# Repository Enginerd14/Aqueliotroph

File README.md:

# Aqueliotroph
Automated plant watering and sun tracking system to optimise conditions for growth

I made this project becuase I always forget to water my plants and they never get enough sunlight. As a result they never survive :(. The Aqueliotroph system directly combats this by moving the plant to optimise light and watering the plant when soil mositure is low. 

Inspiration behind the Name: 

## 3D model

## Schematic

## PCB

# Parts List

> **Note:** Only the PCB needs to be purchased. I already have all other parts available, so the cost should only be around **£5 / $7**.

| Item | Qty | Need to Buy | Price (£) | Link | Total (£) | Total ($) |
|---|---:|:---:|---:|---:|---:|---
| 600mm Aluminium extrusion | 1 | No | £7.00 | [Al extrusion 600mm](https://www.ebay.co.uk/itm/305167092557?var=604105049024) |52.67 |71.84
| Belt Pulley | 1 | No | £4.99 | [Belt Pulley](https://www.aliexpress.com/item/1005010636842055.html) |
| Belt idler | 1 | No | £3.85 | [Idler Pulley](https://www.aliexpress.com/item/1005008093251681.html) |
| V Wheels | 4 | No | £2.44 | [V Wheels](https://www.aliexpress.com/item/1005004275676552.html) |
| Flexible plastic tube | 1 | No | £1.47 | [PVC tube](https://www.aliexpress.com/item/1005009698880250.html) |
| DC motor | 1 | No | £2.12 | [DC pump 12V 60RPM](https://www.ebay.co.uk/itm/226921983677?var=526075182200) |
| DC Water Pump | 1 | No | £2.48 | [DC water pump](https://www.aliexpress.com/item/1005007587818206.html) |
| Limit Switches | 2 | No | £1.23 | [Limit switches](https://www.aliexpress.com/item/1005005924250789.html) |
| Moisture sensor | 1 | No | £2.59 | [Soil moisture sensor](https://www.ebay.co.uk/itm/235973021747?var=536444158439) |
| Wire | 1m | No | £0.80 | [Wire](https://www.aliexpress.com/item/1005007251965003.html) |
| 470µF and 0.1µF Capacitor | 3 | No | £3.99 | [Capacitors](https://www.ebay.co.uk/itm/227351789982?var=526553493681) |
| LCD Display | 1 | No | £2.21 | [LCD](https://www.aliexpress.com/item/1005005095893869.html) |
| 12V 3A power supply | 1 | No | £4.06 | [Power supply 12V 3A](https://www.aliexpress.com/item/4000494270389.html) |
| L293D | 1 | No | £1.36 | [L293D](https://www.aliexpress.com/item/1005010400118009.html) |
| Arduino Uno | 1 | No | £3.22 | [Arduino Uno R3](https://www.aliexpress.com/item/32768431306.html) |
| LDR | 1 | No | £0.84 | [LDR](https://www.aliexpress.com/item/1005008904534544.html) |
| 10K, 220Ω Resistor | 2 | No | £1.75 | [Resistors](https://www.aliexpress.com/item/32698175464.html) |
| 250K Potentiometer | 1 | No | £1.27 | [Potentiometer](https://www.aliexpress.com/item/1005009882075493.html) |
| **PCB** | **1** | **Yes** | **£5.00** | N/A |

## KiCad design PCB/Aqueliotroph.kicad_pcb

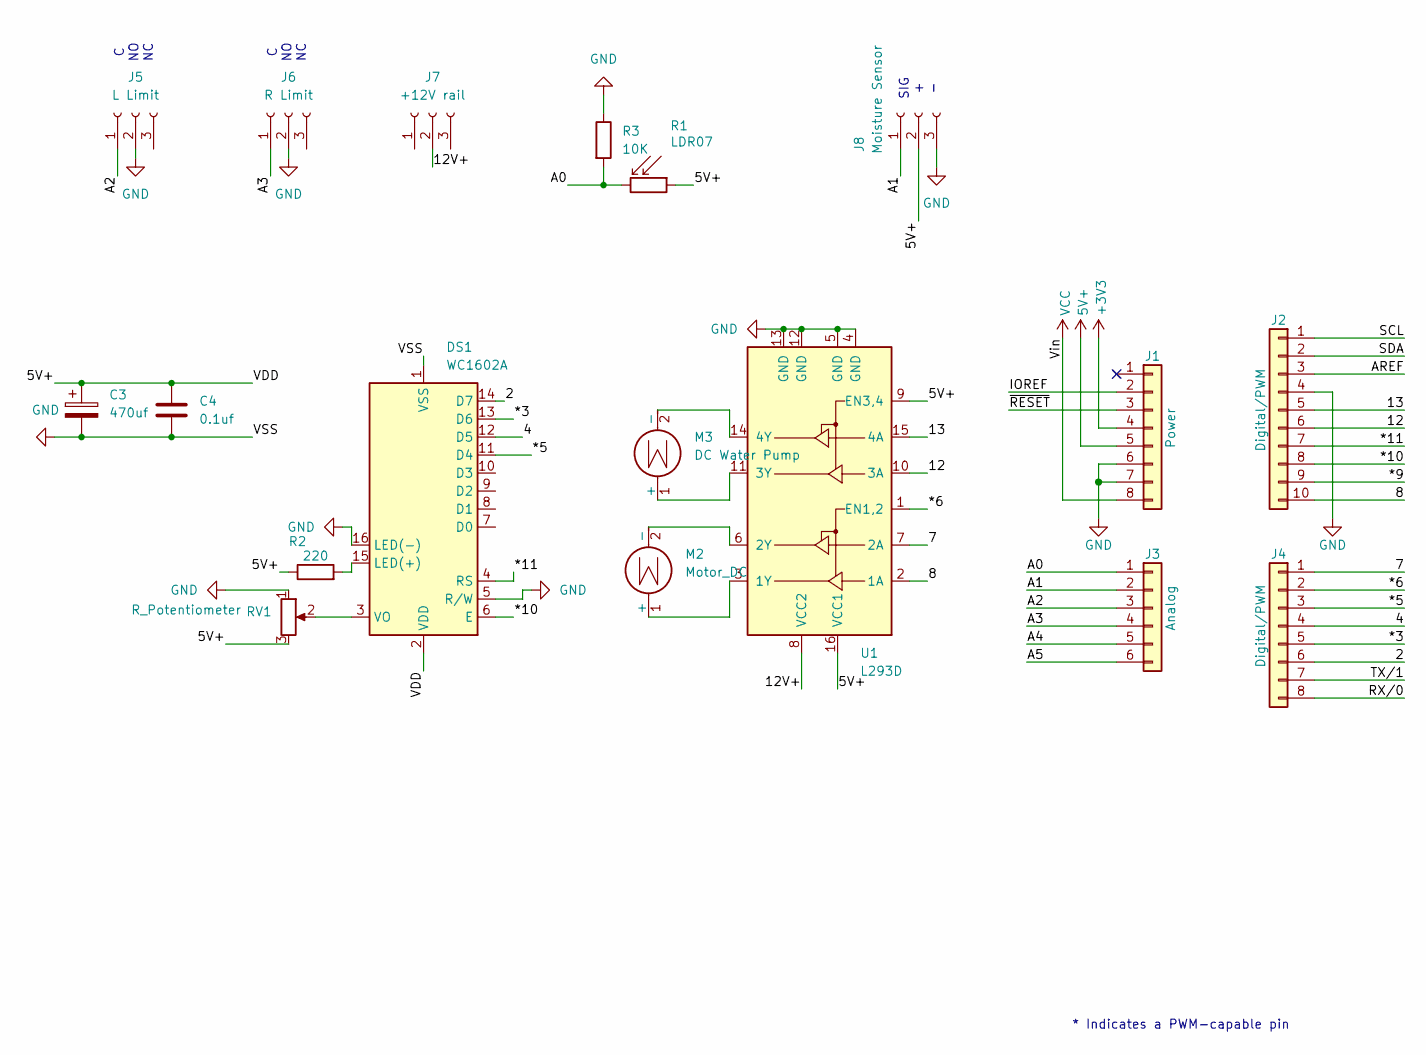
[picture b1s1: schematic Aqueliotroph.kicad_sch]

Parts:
C3: 470uf; C_Radial_D10.0mm_H12.5mm_P5.00mm
C4: 0.1uf; C_Disc_D3.8mm_W2.6mm_P2.50mm
DS1: WC1602A; PinSocket_1x16_P2.54mm_Vertical
J1: Power; PinSocket_1x08_P2.54mm_Vertical
J2: Digital/PWM; PinSocket_1x10_P2.54mm_Vertical
J3: Analog; PinSocket_1x06_P2.54mm_Vertical
J4: Digital/PWM; PinSocket_1x08_P2.54mm_Vertical
J5: L Limit; PinSocket_1x03_P2.54mm_Vertical
J6: R Limit; PinSocket_1x03_P2.54mm_Vertical
J7: +12V rail; PinHeader_1x03_P2.54mm_Vertical
J8: Moisture Sensor; PinSocket_1x03_P2.54mm_Vertical
M2: Motor_DC; PinSocket_1x02_P2.54mm_Vertical
M3: DC Water Pump; PinSocket_1x02_P2.54mm_Vertical
R1: LDR07; PinSocket_1x02_P2.54mm_Vertical
R2: 220; R_Axial_DIN0204_L3.6mm_D1.6mm_P5.08mm_Horizontal
R3: 10K; R_Axial_DIN0204_L3.6mm_D1.6mm_P5.08mm_Horizontal
RV1: R_Potentiometer; Potentiometer_Piher_PT-10-V10_Vertical
U1: L293D; DIP-16_W7.62mm

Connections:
5V+: C3.1, C4.1, DS1.2 (VDD), J1.5, J8.2, R1.1, R2.1, RV1.3, U1.9 (EN3,4), U1.16 (VCC1)
+3V3: J1.4
/2: DS1.14 (D7), J4.6
/4: DS1.12 (D5), J4.4
/7: J4.1, U1.7 (2A)
/8: J2.10, U1.2 (1A)
/12: J2.6, U1.10 (3A)
/12V+: J7.2, U1.8 (VCC2)
/13: J2.5, U1.15 (4A)
/*3: DS1.13 (D6), J4.5
/*5: DS1.11 (D4), J4.3
/*6: J4.2, U1.1 (EN1,2)
/*9: J2.9
/*10: DS1.6 (E), J2.8
/*11: DS1.4 (RS), J2.7
/A0: J3.1, R1.2, R3.2
/A1: J3.2, J8.1
/A2: J3.3, J5.1
/A3: J3.4, J6.1
/A4: J3.5
/A5: J3.6
/AREF: J2.3
/IOREF: J1.2
/RX/0: J4.8
/SCL: J2.1
/SDA: J2.2
/TX/1: J4.7
/~RESET: J1.3
GND: C3.2, C4.2, DS1.1 (VSS), DS1.5 (R/W), DS1.16 (LED(-)), J1.6, J1.7, J2.4, J5.2, J6.2, J8.3, R3.1, RV1.1, U1.4 (GND), U1.5 (GND), U1.12 (GND), U1.13 (GND)
unnamed: DS1.15 (LED(+)), R2.2
unnamed: DS1.3 (VO), RV1.2
unnamed: M2.1 (+), U1.3 (1Y)
unnamed: M2.2 (-), U1.6 (2Y)
unnamed: M3.1 (+), U1.11 (3Y)
unnamed: M3.2 (-), U1.14 (4Y)
VCC: J1.8

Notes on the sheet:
C NO NC
* Indicates a PWM-capable pin
SIG + -

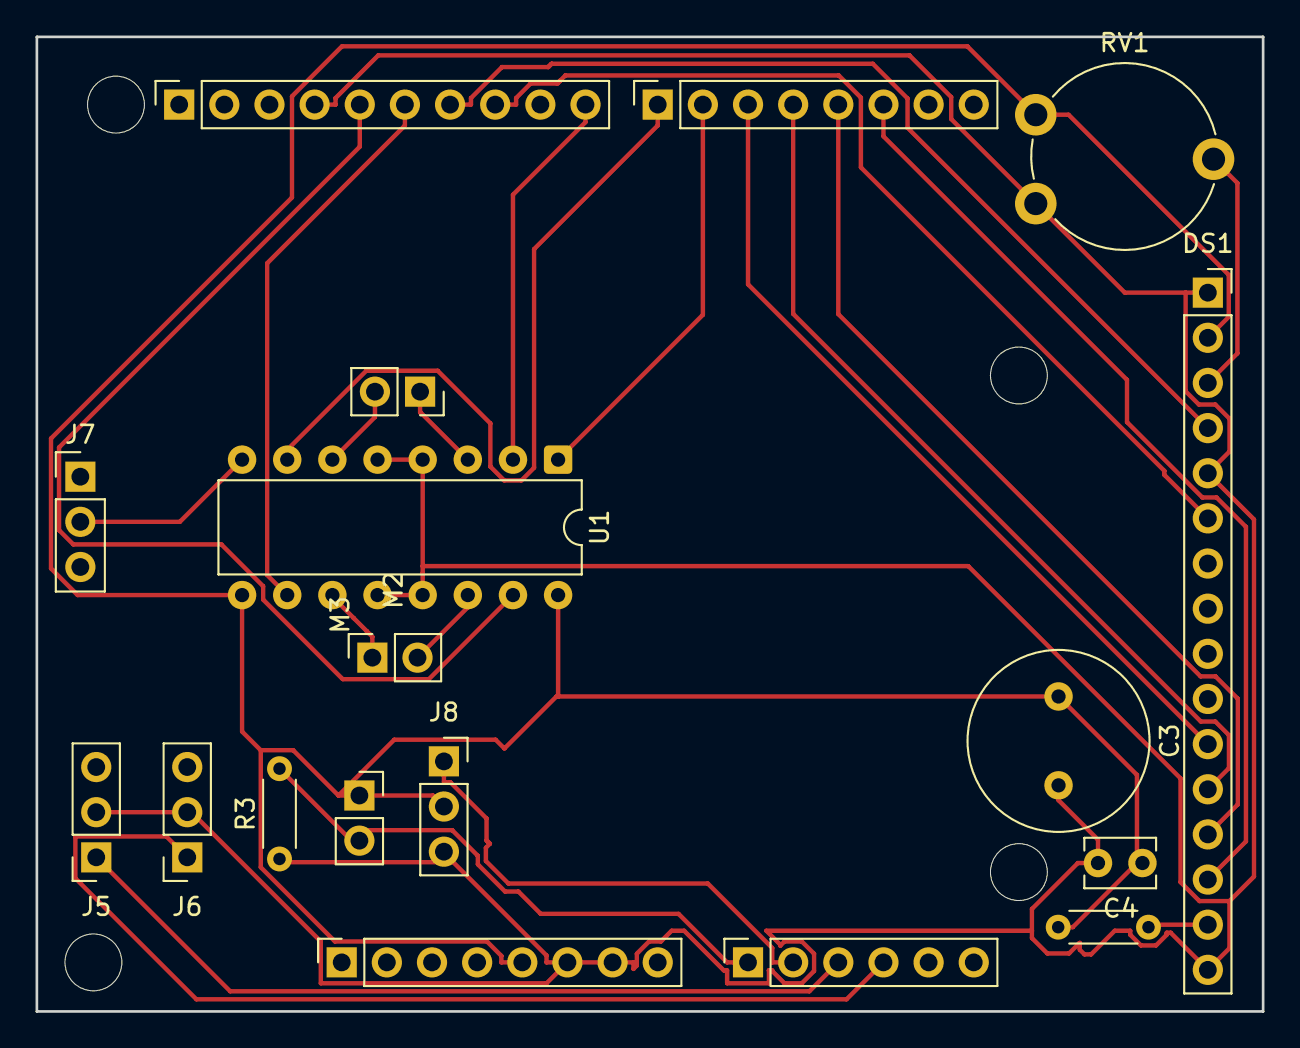
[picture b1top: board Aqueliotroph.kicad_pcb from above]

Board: 2 copper layers, 69.0 x 54.8 mm, 22 parts (0 on the bottom side), 24 nets.

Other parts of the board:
MH1, MH2, MH3, MH4: MountingHole_3.2mm
